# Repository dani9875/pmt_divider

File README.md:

# Photomultiplier tube resistor divider

A photomultiplier tube (PMT) resistor divider is a crucial component in the operation of photomultiplier tubes. These devices are highly sensitive light detectors used in various applications such as medical imaging, nuclear and particle physics, and scientific research.

The resistor divider network within a PMT is designed to ensure proper voltage distribution across the dynodes of the tube. Dynodes are the intermediate electrodes that amplify the signal produced by incident photons. The correct biasing of these dynodes is essential for optimal performance, signal amplification, and minimizing noise.

The typical resistor divider configuration involves a series of resistors connected between the high-voltage supply and ground. Each dynode is connected to a tap between two resistors, thereby establishing the necessary potential differences.

# Release
You can find the manufacturing files in the release folder and additional documentations in the docs folder.

### Version: v1.0
Changelog:
- Initial PCB design to replicate functionality of a PMT resistor divider circuitry. 

Disclaimer: The PCB described herein has not been manufactured or tested. Users are advised to thoroughly review all design and manufacturing files prior to any application or implementation. If you happen to find any design flaws or problems, please contact me.

## List of potentional improvements
- [ ] Release artifact manf. output resistor does not get rendered

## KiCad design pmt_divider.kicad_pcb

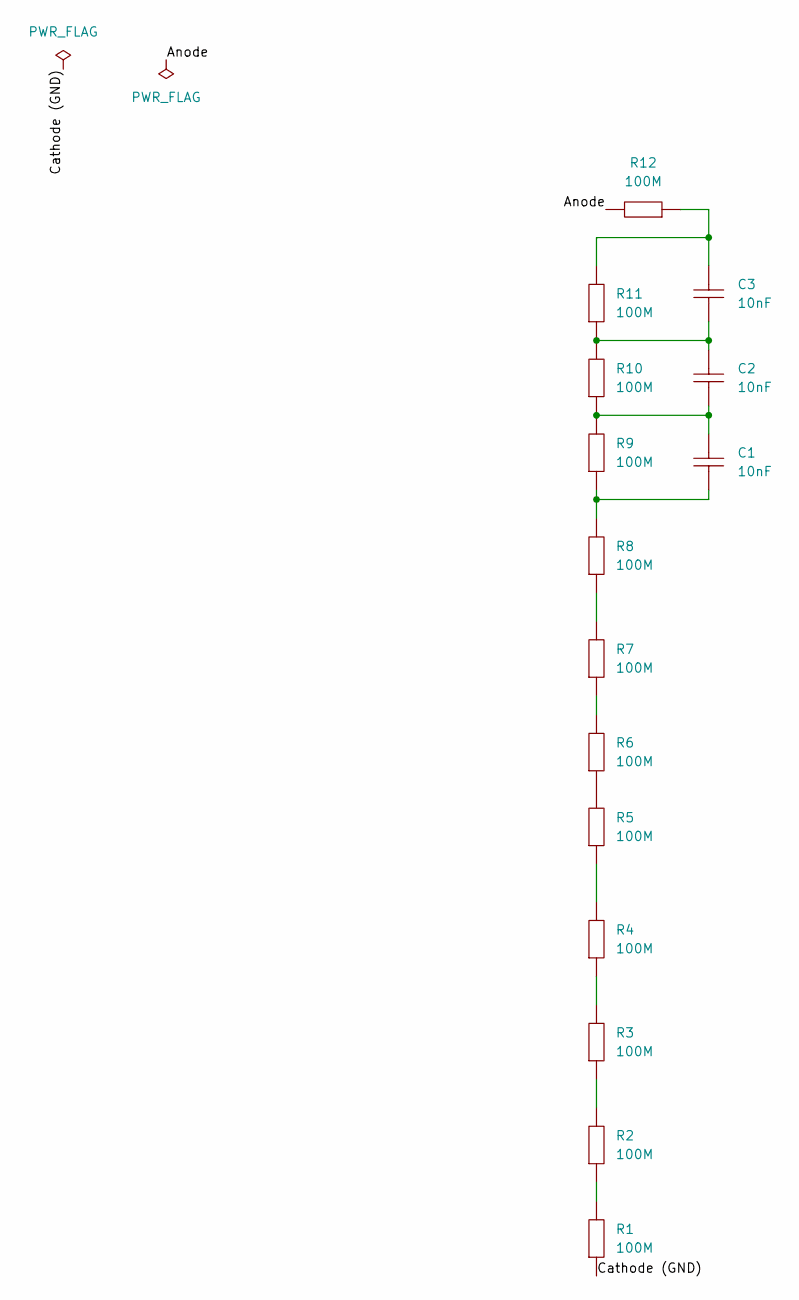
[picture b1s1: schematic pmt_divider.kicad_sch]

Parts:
C1, C2, C3: CC0805KKX7RBBB103; [CAP_SMD_0805_2012Metric]; LCSC Part C106840
R1, R2, R3, R4, R5, R6, R7, R8, R9, R10, R11, R12: 1206W4F0000T5E; [RES_SMD_1206_3216Metric]; LCSC Part C2076408

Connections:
/Anode: R12.2
/Cathode (GND): R1.1
unnamed: C1.1, R8.2, R9.1
unnamed: C1.2, C2.1, R9.2, R10.1
unnamed: C2.2, C3.1, R10.2, R11.1
unnamed: C3.2, R11.2, R12.1
unnamed: R1.2, R2.1
unnamed: R2.2, R3.1
unnamed: R3.2, R4.1
unnamed: R4.2, R5.1
unnamed: R5.2, R6.1
unnamed: R6.2, R7.1
unnamed: R7.2, R8.1

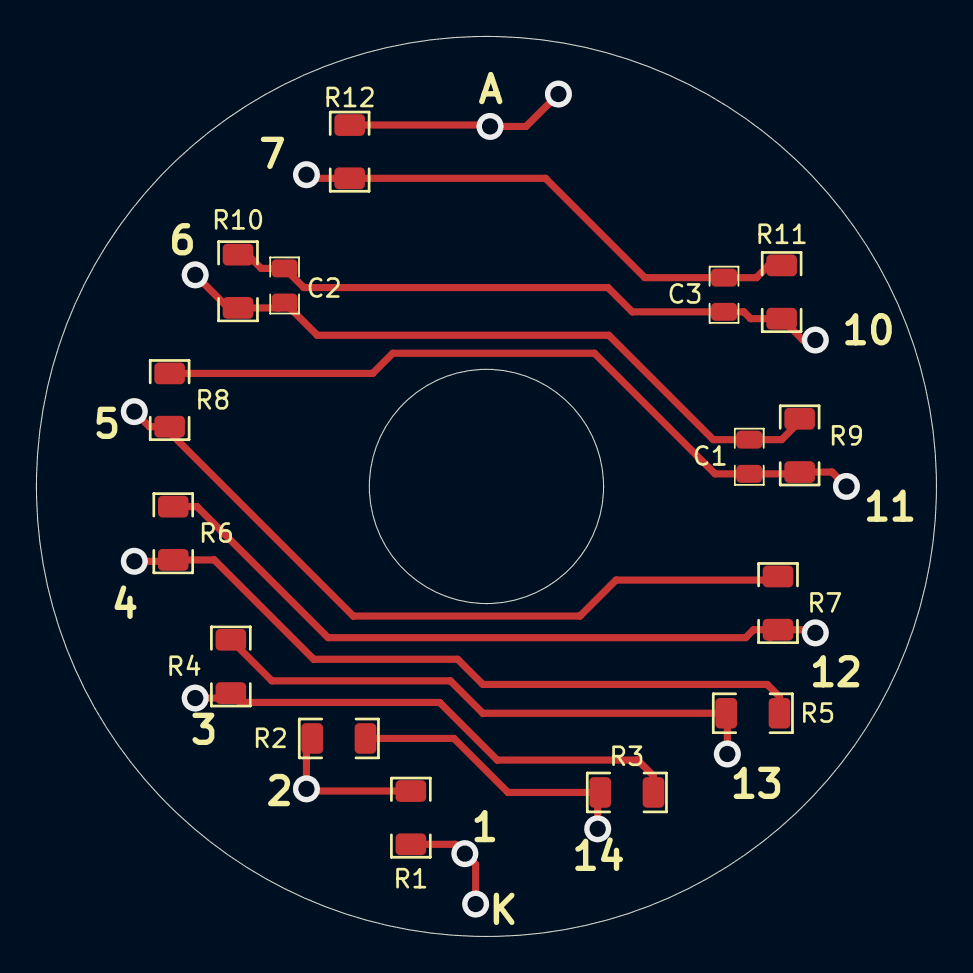
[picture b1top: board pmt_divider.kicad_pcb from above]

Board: 2 copper layers, 50.0 x 50.0 mm, 15 parts (0 on the bottom side), 11 nets.

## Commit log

2024-07-26 Readme change, LICENSE owner filled and docs
2024-07-26 Impr. added in README
